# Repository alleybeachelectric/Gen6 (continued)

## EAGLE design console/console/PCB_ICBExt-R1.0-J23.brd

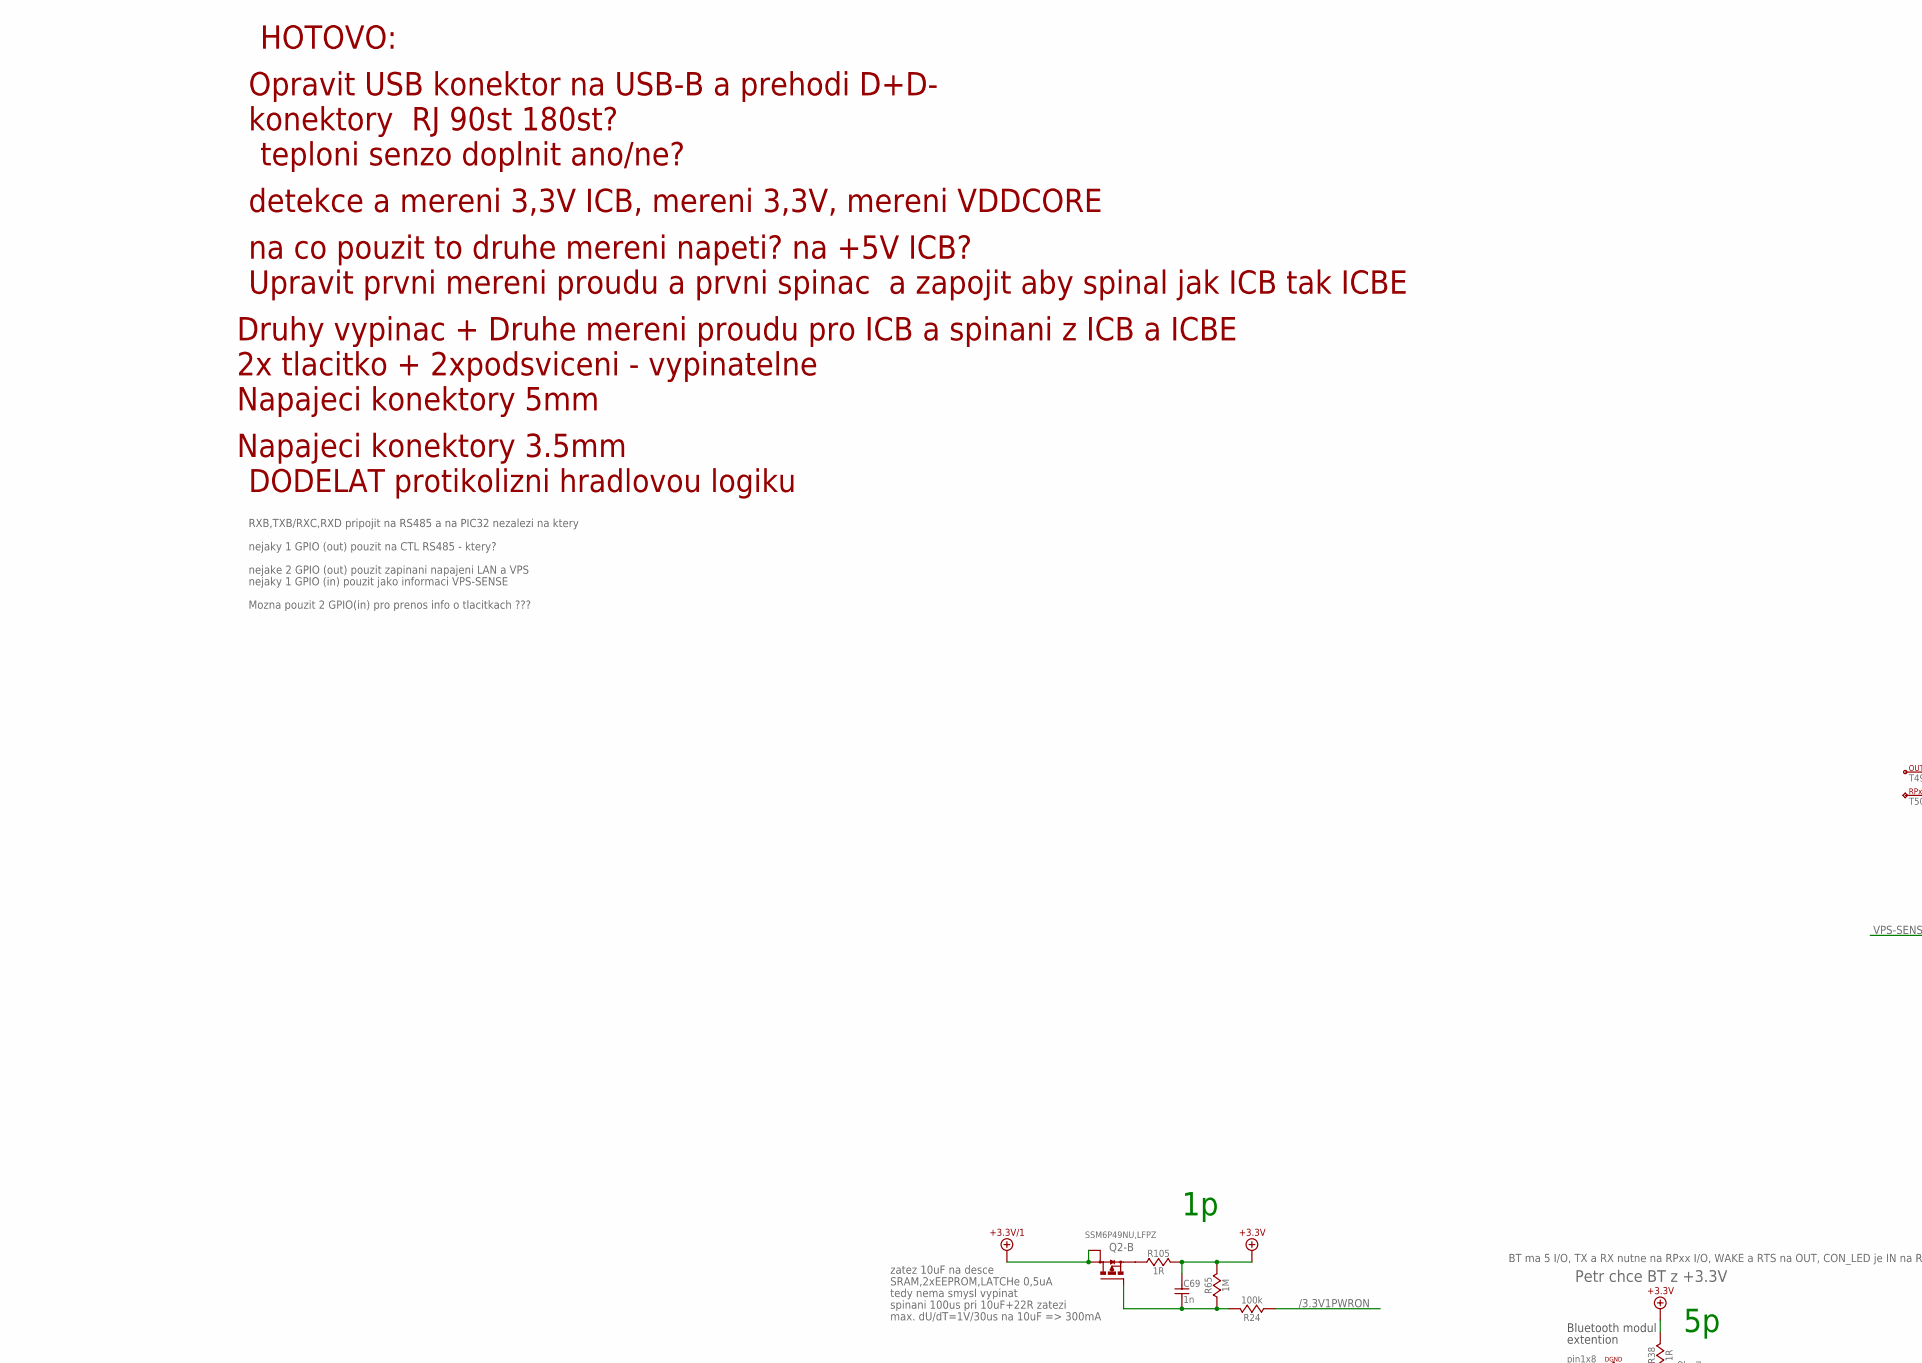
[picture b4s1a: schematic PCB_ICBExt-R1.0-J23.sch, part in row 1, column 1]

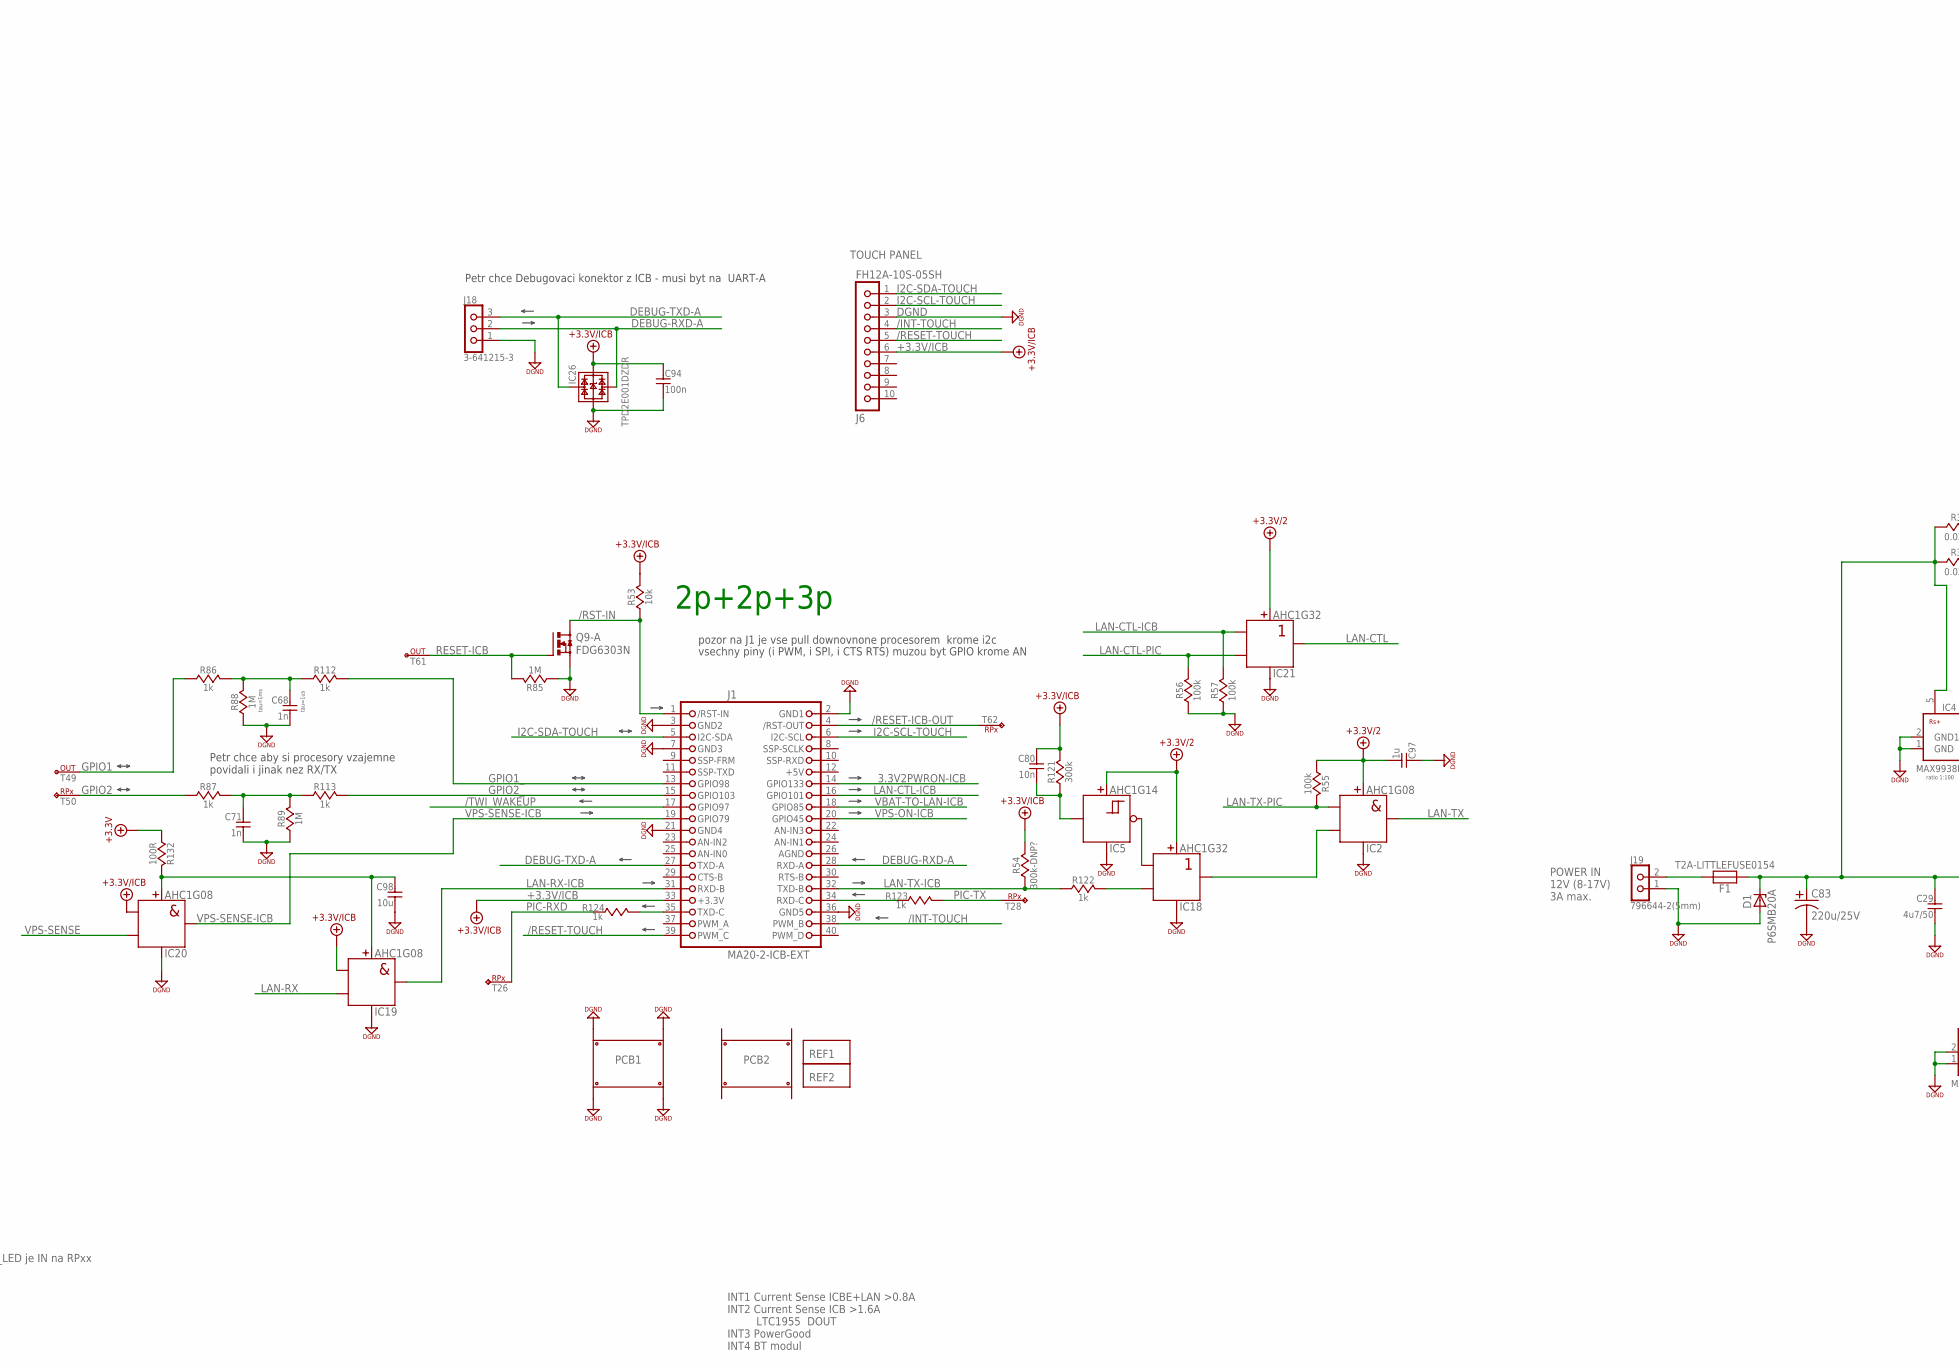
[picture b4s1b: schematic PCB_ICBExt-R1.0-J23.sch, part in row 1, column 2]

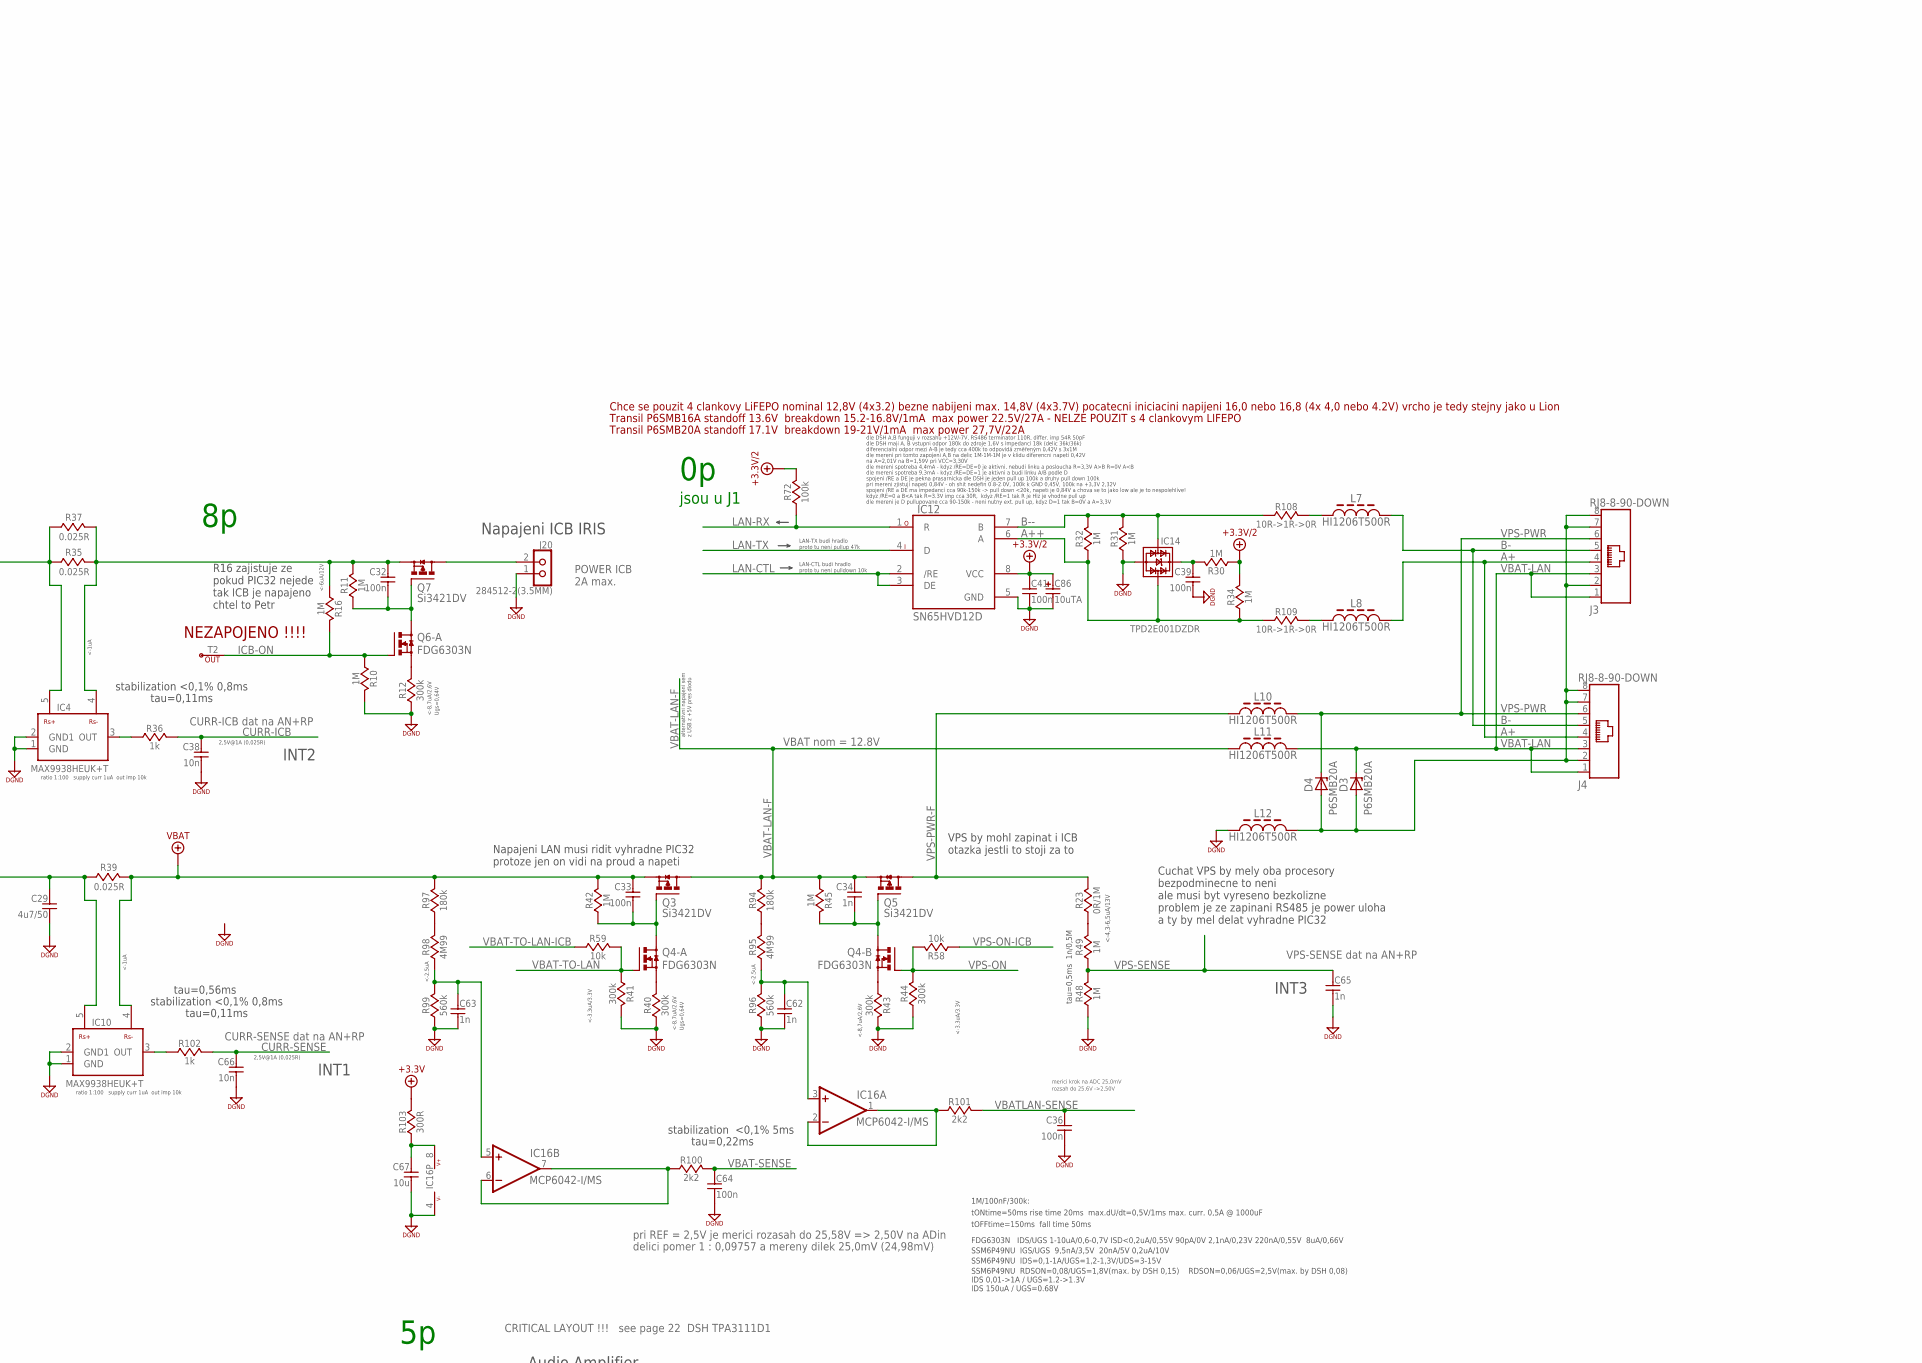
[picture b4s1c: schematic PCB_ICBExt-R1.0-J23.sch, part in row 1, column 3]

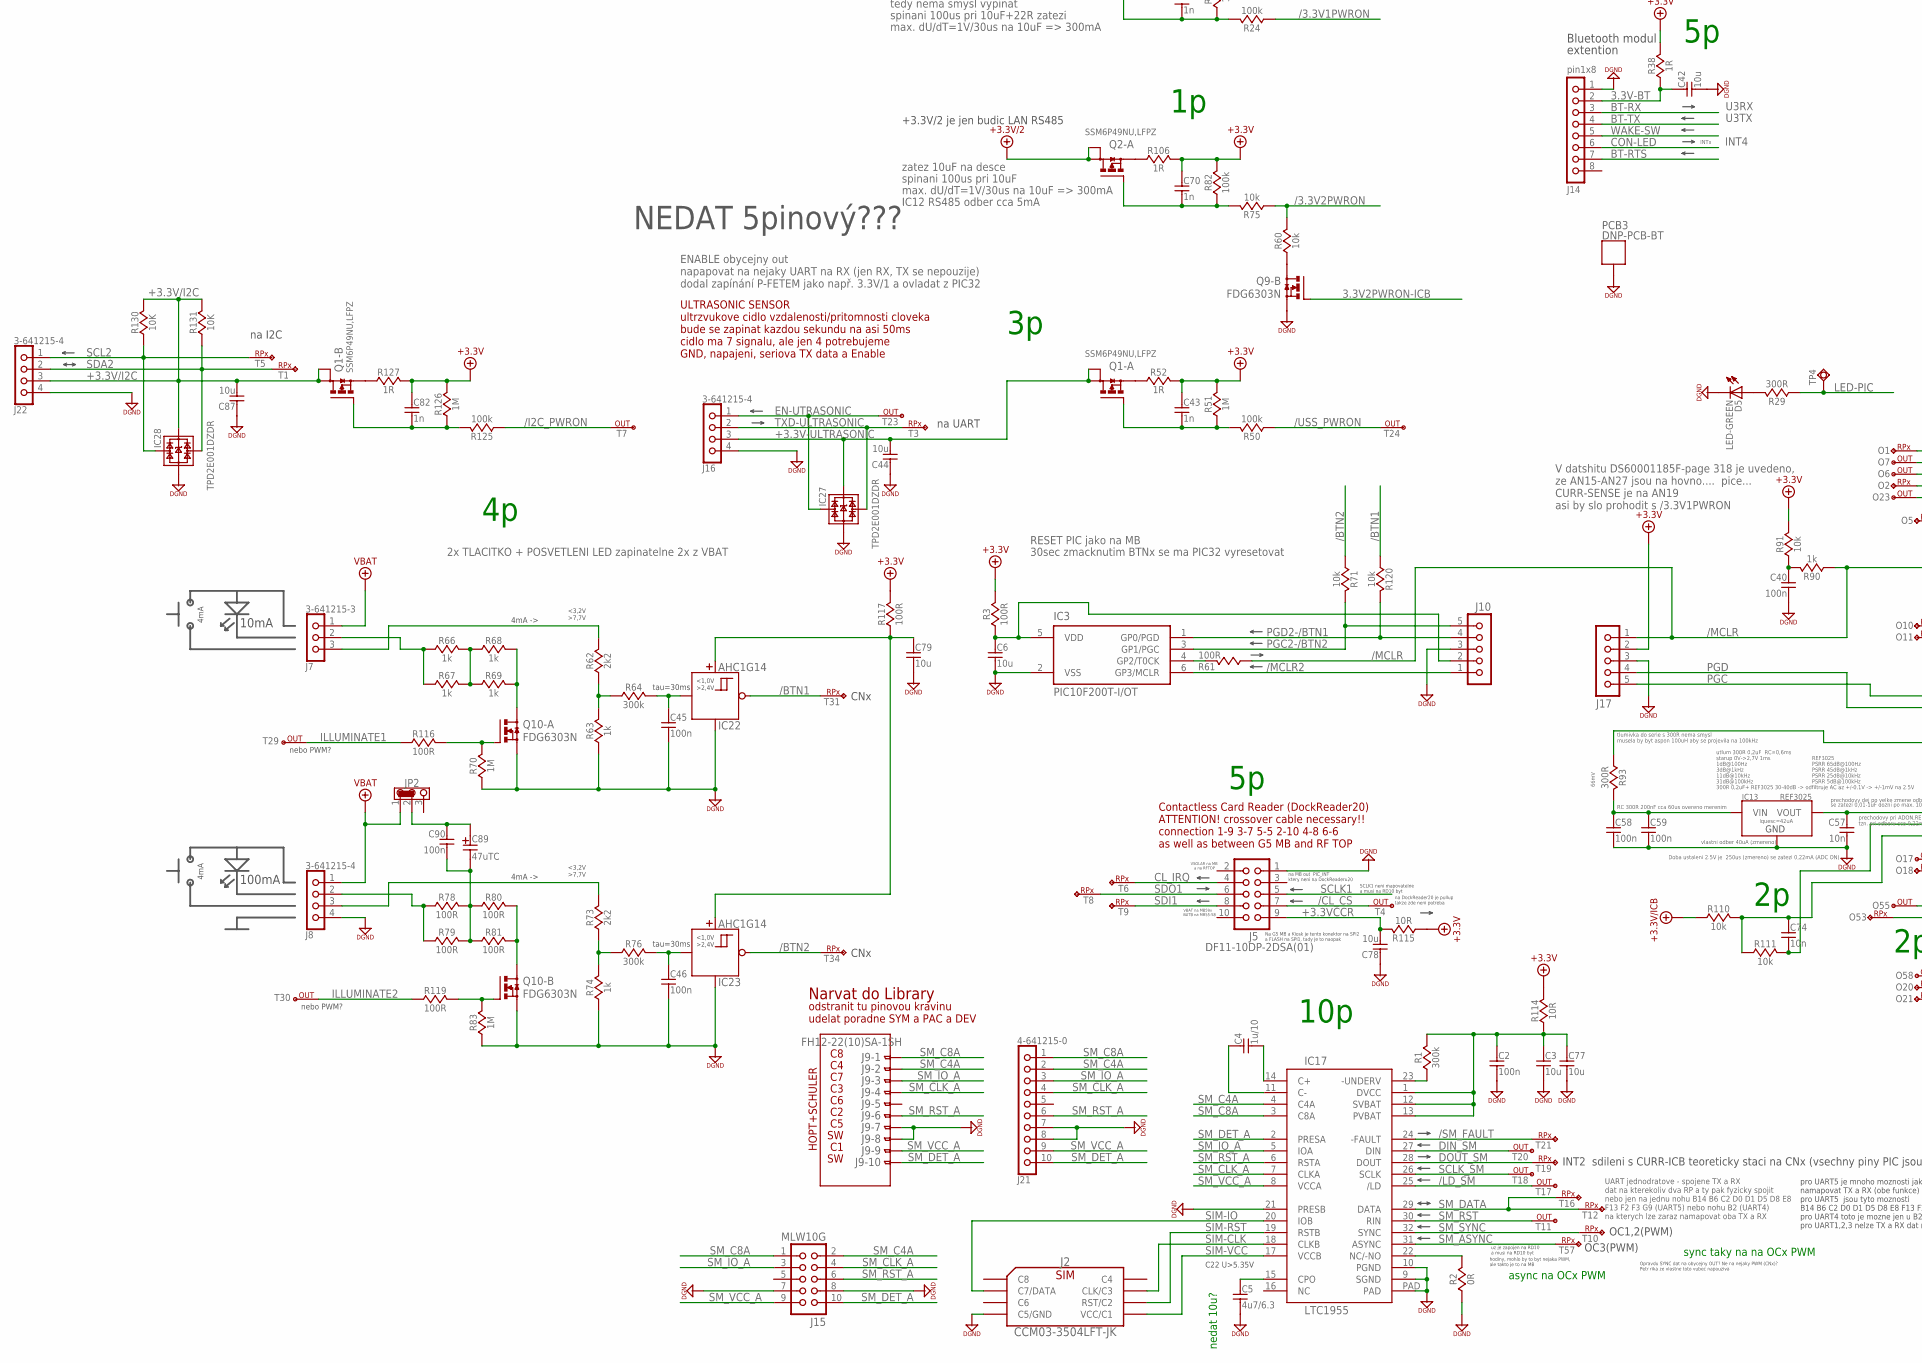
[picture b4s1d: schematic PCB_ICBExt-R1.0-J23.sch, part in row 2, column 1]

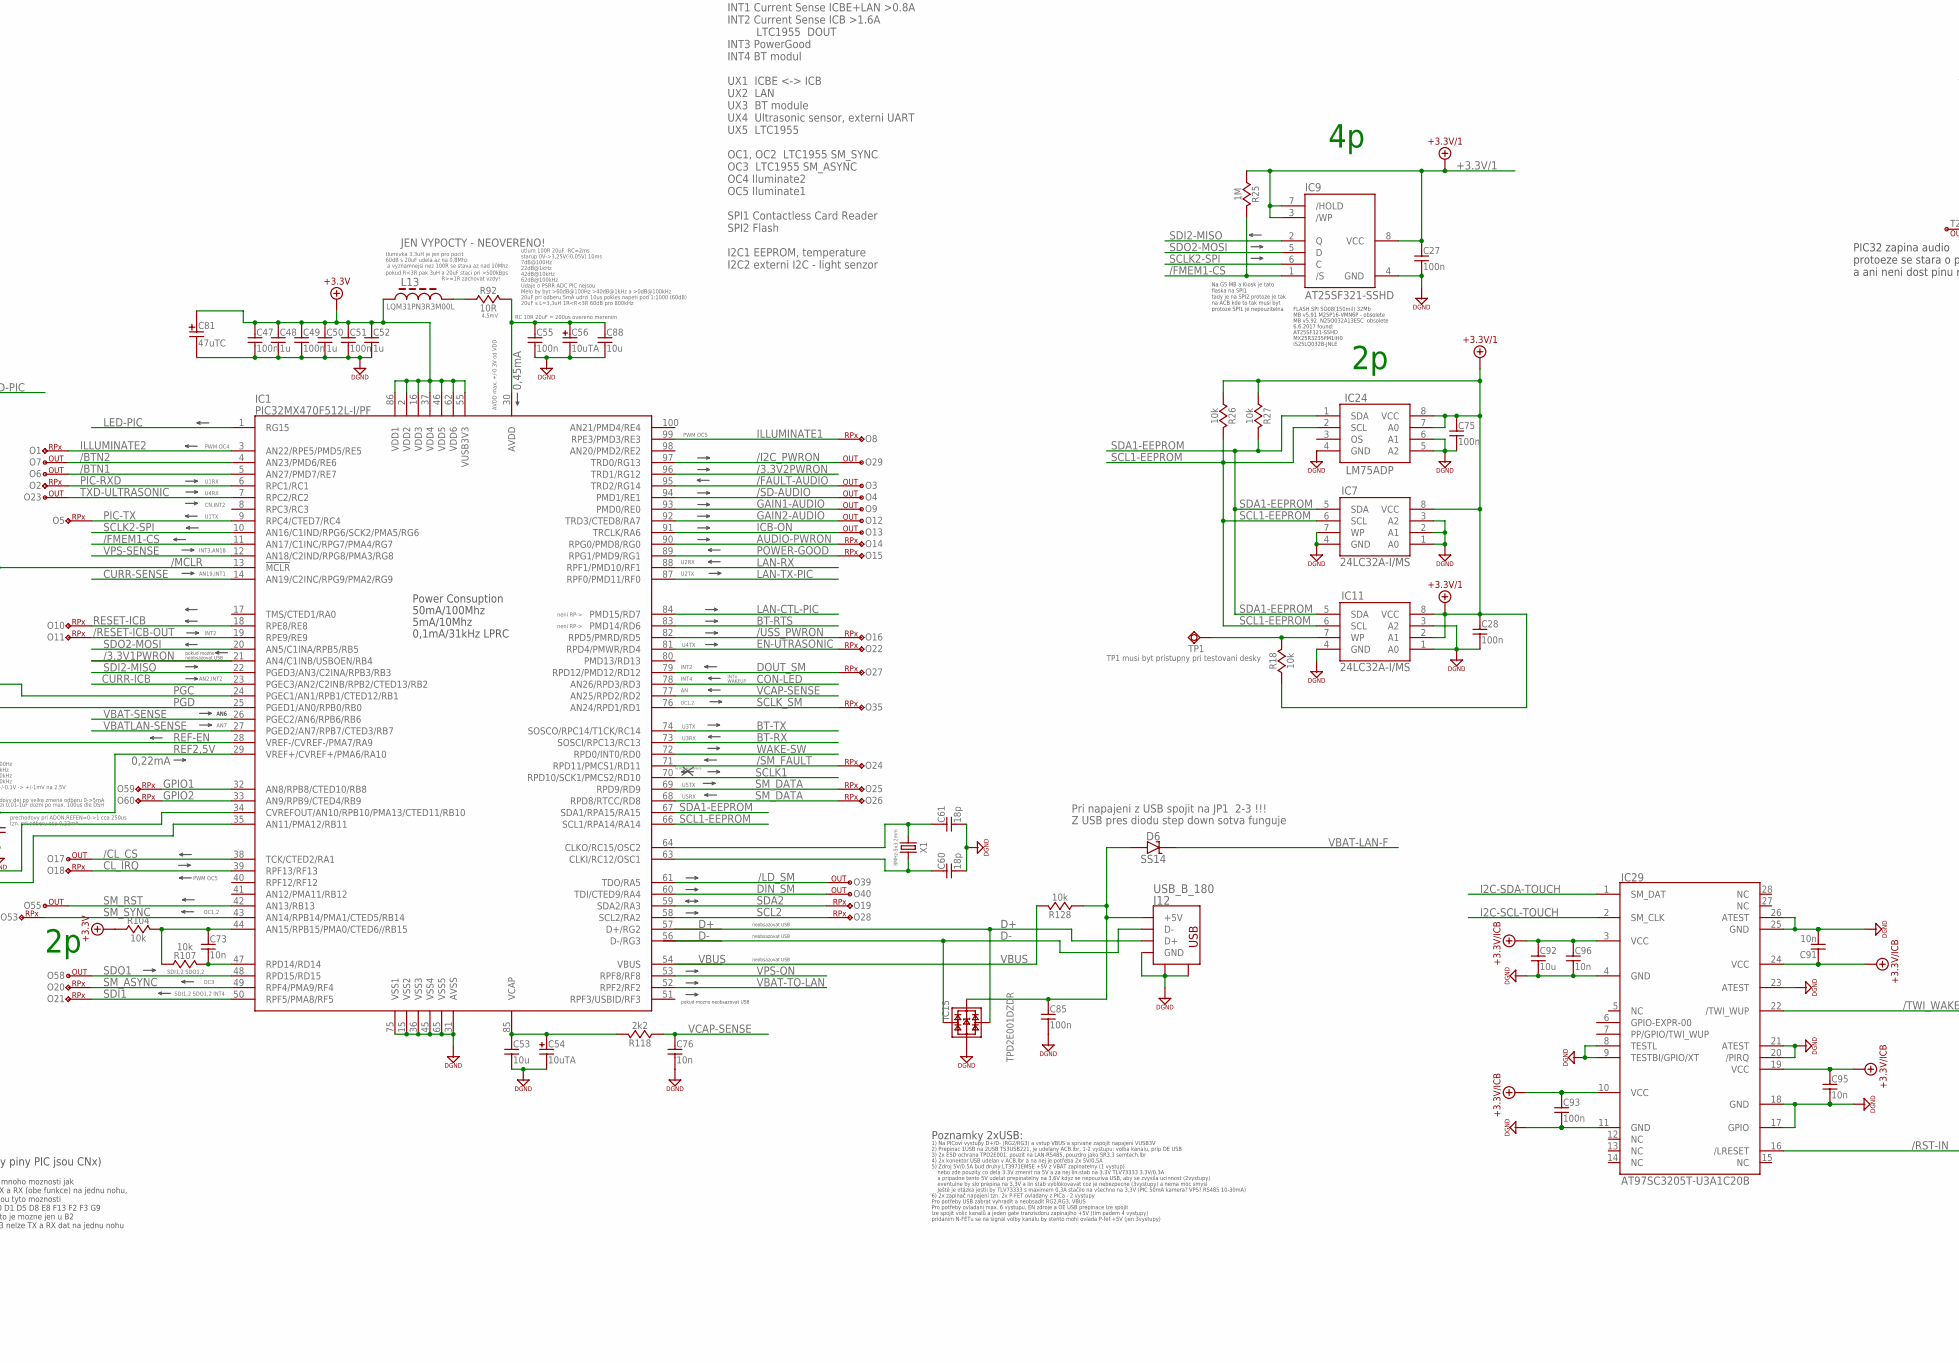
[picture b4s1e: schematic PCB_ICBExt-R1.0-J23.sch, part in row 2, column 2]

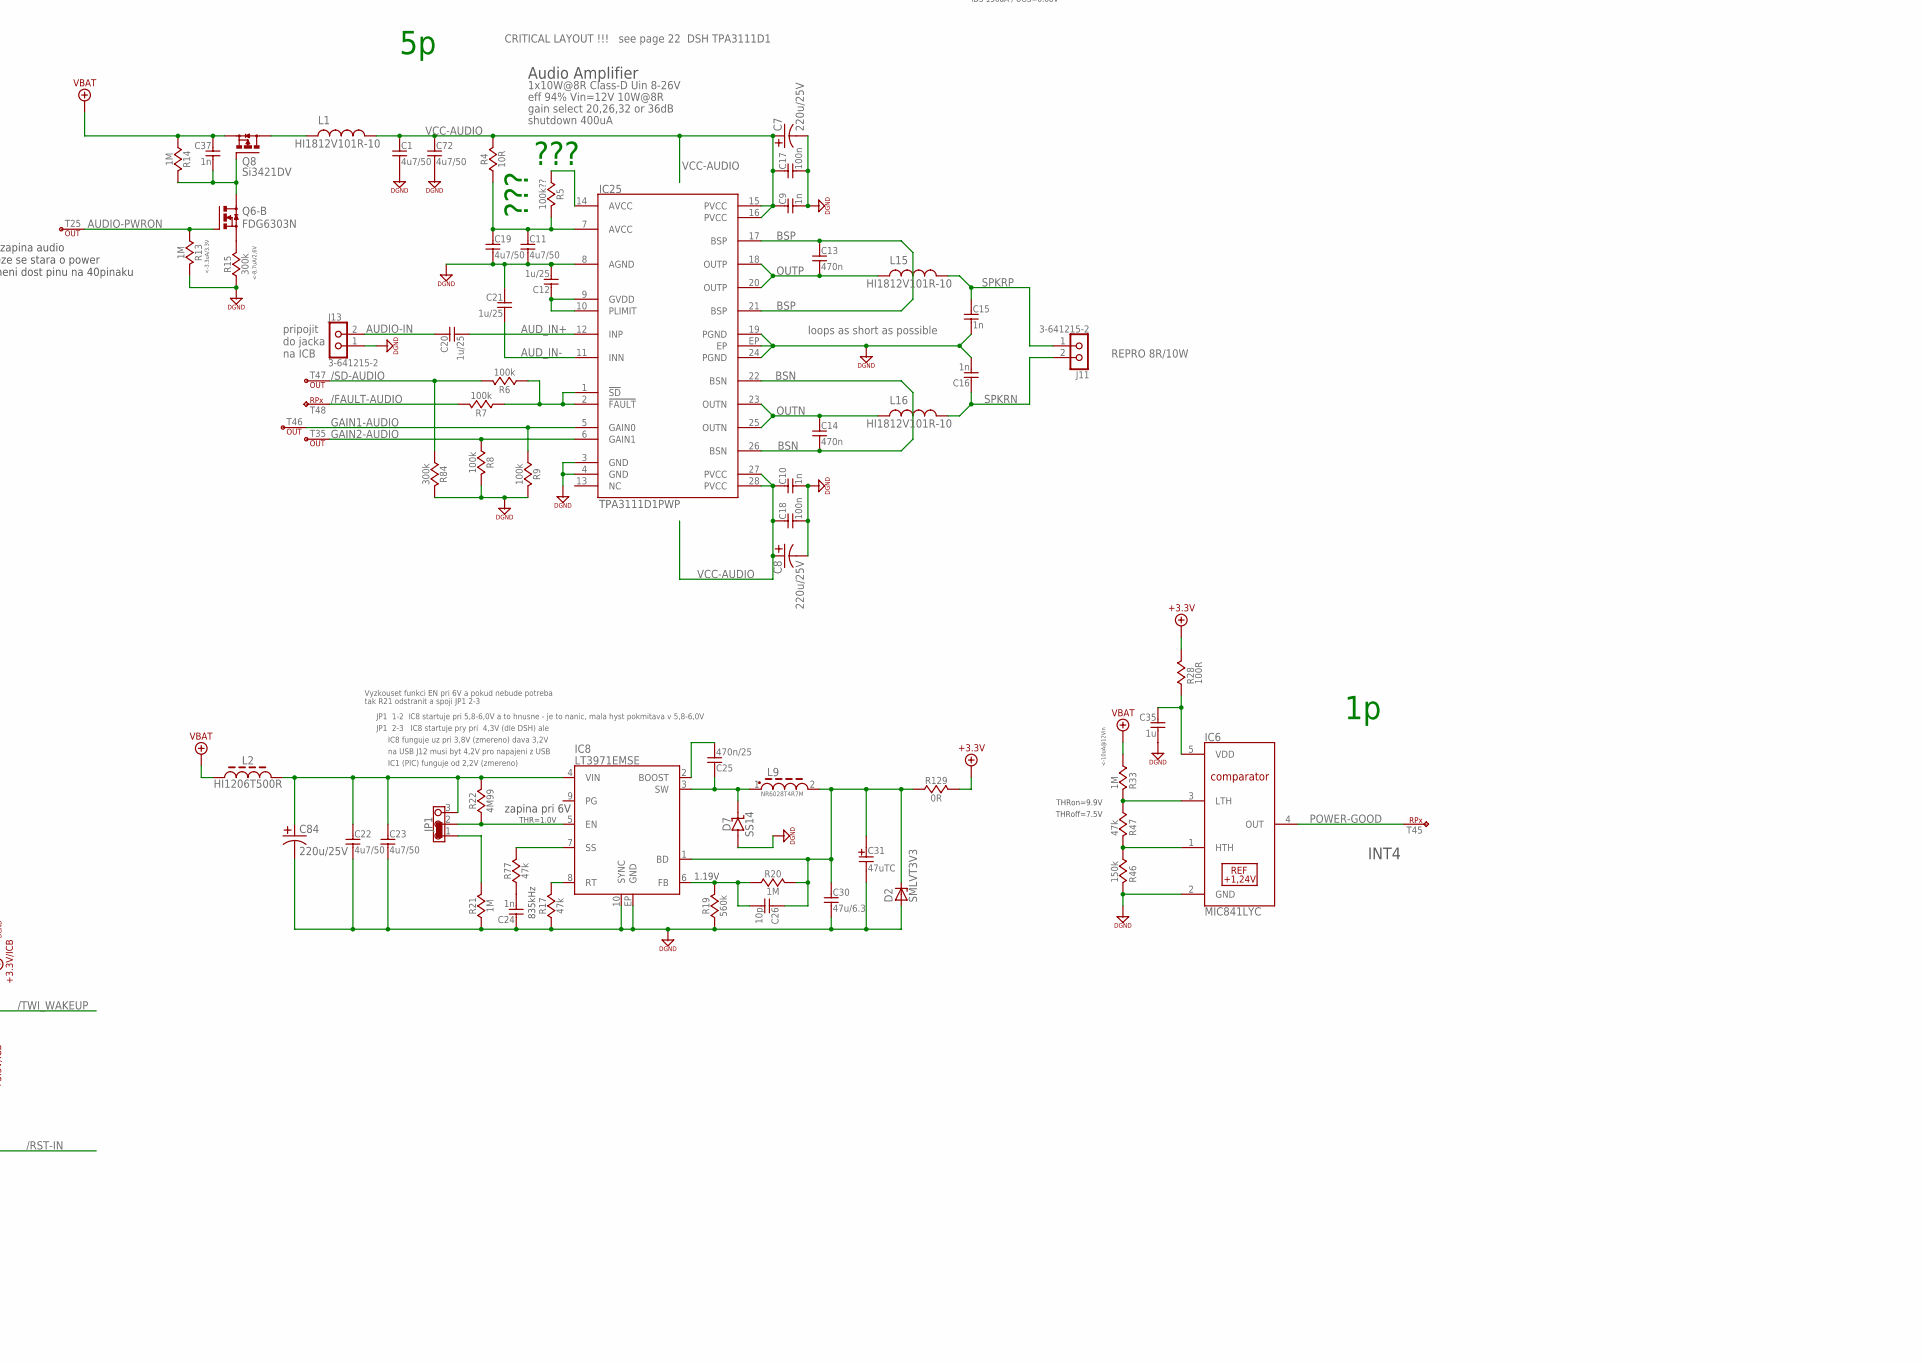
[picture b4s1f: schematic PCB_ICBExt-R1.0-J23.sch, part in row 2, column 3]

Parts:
C1, C11, C19, C22, C23, C29, C72: 4u7/50; 1206
C2, C17, C18, C27, C28, C32, C33, C36, C39, C40, C41, C45, C46, C47, C49, C51, C55, C58, C59, C64, C75, C85, C90, C93, C94: 100n; 0603
C3, C6, C42, C44, C53, C67, C77, C78, C79, C87, C88, C92, C98: 10u; 0603
C4: 1u/10; 0603
C5: 4u7/6.3; 0603
C7, C8, C83, C84: 220u/25V; CAP_8MM_DIA_SMT
C9, C10, C15, C16, C24, C34, C37, C43, C62, C63, C65, C68, C69, C70, C71, C82: 1n; 0603
C12, C20, C21: 1u/25; 0603
C13, C14: 470n; 0603
C25: 470n/25; 0603
C26: 10p; 0603
C30: 47u/6.3; 1206
C31, C81, C89: 47uTC; CT-C
C35, C48, C50, C52, C97: 1u; 0603
C38, C57, C66, C73, C74, C76, C80, C91, C95, C96: 10n; 0603
C54, C56, C86: 10uTA; 1206-POL-C
C60, C61: 18p; 0603
D1, D3, D4: P6SMB20A; SMB
D2: SMLVT3V3; SMA
D5: LED-GREEN; 0805-POL-D
D6, D7: SS14; SMA
F1: T2A-LITTLEFUSE0154; LITTLEFUSE0154
IC1: PIC32MX470F512L-I/PF; TQFP100_14X14_0,5MM
IC2, IC19, IC20: AHC1G08; SC70-5,SOT353,TSSOP5
IC3: PIC10F200T-I/OT; SOT23-6
IC4, IC10: MAX9938HEUK+T; SOT23-5
IC5, IC22, IC23: AHC1G14; SC70-5,SOT353,TSSOP5
IC6: MIC841LYC; SC-70-5
IC7, IC11: 24LC32A-I/MS; MSOP-08
IC8: LT3971EMSE; MSOP10EXP
IC9: AT25SF321-SSHD; SO-08
IC12: SN65HVD12D; SO08
IC13: REF3025; SOT23
IC14, IC15, IC26, IC27, IC28: TPD2E001DZDR; SOT-143
IC16: MCP6042-I/MS; MSOP-08
IC17: LTC1955; QFN32
IC18, IC21: AHC1G32; SC70-5,SOT353,TSSOP5
IC24: LM75ADP; TSSOP08-3
IC25: TPA3111D1PWP; TSSOP28_EP
IC29: AT97SC3205T-U3A1C20B; TSSOP28
J1: MA20-2-ICB-EXT; MA20-2
J2: CCM03-3504LFT-JK
J3, J4: RJ8-8-90-DOWN
J5: DF11-10DP-2DSA(01); DF11-10DP-2DSA
J6: FH12A-10S-05SH
J7, J18: 3-641215-3
J8, J16, J22: 3-641215-4
J9: FH12-22(10)SA-1SH; CON-FPC-1.0MM-10POS
J10, J17: DNP-open-hole; MA05-1
J11, J13: 3-641215-2
J12: USB_B_180; USB_B_90
J14: pin1x8; MA08-1-MALE
J15: MLW10G; MLW10G-5X2
J19: 796644-2(5mm); 796644-2-5MM
J20: 284512-2(3.5MM); 284512-2-3,5MM
J21: 4-641215-0
JP1, JP2: JP3CLOSE12
L1, L15, L16: HI1812V101R-10; L1812; MFR_PN HI1812V101R-10
L2, L7, L8, L10, L11, L12: HI1206T500R; 1206
L9: NR6028T4R7M; NR6028
L13: LQM31PN3R3M00L; 1206
O1, O2, O5, O8, O10, O11, O14, O15, O16, O18, O19, O20, O21, O22, O24, O25, O26, O27, O28, O35, O53, O59, O60: PIC-RPX; TEMP-PAD
O3, O4, O6, O7, O9, O12, O13, O17, O23, O29, O39, O40, O55, O58: PIC-OUT; TEMP-PAD
PCB1: PCB-ICBE
PCB2: NDP-PCB-ICB; PCB-ICB
PCB3: DNP-PCB-BT; BT_MODULE_BRD
Q1, Q2: SSM6P49NU,LFPZ; MICRO_FET
Q3, Q5, Q7, Q8: Si3421DV; SSOT-6
Q4, Q6, Q9, Q10: FDG6303N; SC70-6
R1, R12, R15, R40, R41, R43, R44, R64, R76, R84, R121: 300k; 0603
R2, R129: 0R; 0603
R3, R28, R61, R78, R79, R80, R81, R116, R117, R119, R132: 100R; 0603
R4, R92, R114, R115: 10R; 0603
R5: 100k??; 0603
R6, R7, R8, R9, R24, R50, R55, R56, R57, R72, R82, R125: 100k; 0603
R10, R11, R13, R14, R16, R20, R21, R25, R30, R31, R32, R33, R34, R42, R45, R48, R49, R51, R65, R70, R83, R85, R88, R89, R126: 1M; 0603
R17, R47, R77: 47k; 0603
R18, R26, R27, R53, R58, R59, R60, R71, R75, R91, R104, R107, R110, R111, R120, R128: 10k; 0603
R19, R96, R99: 560k; 0603
R22, R95, R98: 4M99; 0603
R23: 0R/1M; 0603
R29, R93, R103: 300R; 0603
R35, R37, R39: 0.025R; 0805
R36, R63, R66, R67, R68, R69, R74, R86, R87, R90, R102, R112, R113, R122, R123, R124: 1k; 0603
R38, R52, R105, R106, R127: 1R; 0805
R46: 150k; 0603
R54: 300k-DNP?; 0603
R62, R73, R100, R101, R118: 2k2; 0603
R94, R97: 180k; 0603
R108, R109: 10R->1R->0R; 0603
R130, R131: 10K; 0603
REF1, REF2: REF
T1, T3, T5, T6, T8, T9, T10, T12, T16, T19, T21, T26, T28, T31, T34, T45, T48, T50, T57, T62: PIC-RPX; TEMP-PAD
T2, T4, T7, T11, T17, T18, T20, T23, T24, T25, T29, T30, T35, T46, T47, T49, T61: PIC-OUT; TEMP-PAD
TP1: DNP-TestPoint; SMD_ROUND_1MM
TP4: DNP-TestPoint; TH_ROUND_14MM08MM
X1: 8MHz-5x3.2mm; 7B

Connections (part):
3.3V2PWRON-ICB: J1.14 (GPIO133), Q9.5 (G)
3.3V-BT: C42.1, J14.2, R38.1
+3,3V-FILT: C35.1, IC6.5 (VDD), R28.1
+3.3V: C43.1, C47.1, C48.1, C49.1, C50.1, C51.1, C52.1, C69.1, C70.1, C81.+, C82.1, IC1.2 (VDD2), IC1.16 (VDD3), IC1.37 (VDD4), IC1.46 (VDD5), IC1.55 (VUSB3V3), IC1.62 (VDD6), IC1.86 (VDD1), J17.2, L13.1, R3.1, R28.2, R38.2, R51.1, R52.2, R65.1, R82.1, R91.2, R103.2, R104.1, R105.2, R106.2, R114.1, R115.2, R117.2, R126.1, R127.2, R129.1, R132.1
+3.3V-ULTRASONIC: C44.2, IC27.4, J16.3, Q1.6 (D), Q1.P1 (D1)
+3.3V/1: C27.1, C28.1, C75.1, IC7.8 (VCC), IC9.3 (/WP), IC9.7 (/HOLD), IC9.8 (VCC), IC11.2 (A1), IC11.8 (VCC), IC24.7 (A0), IC24.8 (VCC), Q2.3 (D), Q2.P2 (D1), R18.1, R25.2, R26.1, R27.1
+3.3V/2: C41.1, C86.+, C97.2, IC2.5 (VCC), IC5.5 (VCC), IC12.8 (VCC), IC18.5 (VCC), IC21.5 (VCC), Q2.6 (D), Q2.P1 (D1), R30.2, R34.1, R55.1, R72.1
+3.3V/I2C: C87.2, IC28.4, J22.3, Q1.3 (D), Q1.P2 (D1), R130.1, R131.1
+3.3V/ICB: C80.1, C91.1, C92.1, C93.1, C94.1, C95.1, C96.1, IC19.1 (A), IC20.1 (A), IC26.4, IC29.3 (VCC), IC29.10 (VCC), IC29.19 (VCC), IC29.24 (VCC), J1.33 (+3.3V), J6.6, R53.2, R54.2, R110.1, R121.2
+3.3VCCR: C78.2, J5.9, R115.1
/3.3V1PWRON: IC1.21 (AN4/C1INB/USBOEN/RB4), R24.2
/3.3V2PWRON: IC1.96 (TRD1/RG12), R60.2, R75.2
/BTN1: IC1.5 (AN27/PMD7/RE7), IC22.4 (OUT), O6.P$1, R120.2, T31.P$1
/BTN2: IC1.4 (AN23/PMD6/RE6), IC23.4 (OUT), O7.P$1, R71.2, T34.P$1
/CL_CS: IC1.38 (TCK/CTED2/RA1), J5.7, O17.P$1, T4.P$1
/FAULT-AUDIO: IC1.95 (TRD2/RG14), O3.P$1, R7.1, T48.P$1
/FMEM1-CS: IC1.11 (AN17/C1INC/RPG7/PMA4/RG7), IC9.1 (/S), R25.1
/I2C_PWRON: IC1.97 (TRD0/RG13), O29.P$1, R125.2, T7.P$1
/INT-TOUCH: J1.38 (PWM_B), J6.4
/LD_SM: IC1.61 (TDO/RA5), IC17.25 (/LD), O39.P$1, T17.P$1
/MCLR: IC1.13 (!MCLR), J17.1, R61.2, R90.2
/MCLR2: IC3.6 (GP3/MCLR), J10.1
/RESET-ICB-OUT: IC1.19 (RPE9/RE9), J1.4 (/RST-OUT), O11.P$1, T62.P$1
/RESET-TOUCH: J1.39 (PWM_C), J6.5
/RST-IN: IC29.16 (/LRESET), J1.1 (/RST-IN), Q9.6 (D), R53.1
/SD-AUDIO: IC1.94 (PMD1/RE1), O4.P$1, R6.1, R84.2, T47.P$1
/SM_FAULT: IC1.71 (RPD11/PMCS1/RD11), IC17.24 (-FAULT), O24.P$1, T21.P$1
/TWI_WAKEUP: IC29.22 (/TWI_WUP), J1.17 (GPIO97)
/USS_PWRON: IC1.82 (RPD5/PMRD/RD5), O16.P$1, R50.2, T24.P$1
A+: J3.4, J4.4, L8.2
A++: IC12.6 (A), IC14.3, R32.2, R34.2, R109.2
AUD-AVCC: C11.1, C19.1, IC25.7 (AVCC), R4.2, R5.1
AUDIO-IN: C20.1, J13.2
AUDIO-PWRON: IC1.90 (RPG0/PMD8/RG0), O14.P$1, Q6.5 (G), R13.1, T25.P$1
AUD_AMP_FAULT#: IC25.1 (!SD), IC25.2 (!FAULT), R6.2, R7.2
AUD_GVDD: C12.1, IC25.9 (GVDD), IC25.10 (PLIMIT)
AUD_IN+: C20.2, IC25.12 (INP)
AUD_IN-: C21.2, IC25.11 (INN)
AVDD: C55.1, C56.+, C88.1, IC1.30 (AVDD), R92.2
B-: J3.5, J4.5, L7.2
B--: IC12.7 (B), IC14.2, R31.1, R32.1, R108.2
BSN: C14.2, IC25.22 (BSN), IC25.26 (BSN)
BSP: C13.1, IC25.17 (BSP), IC25.21 (BSP)
BT-RTS: IC1.83 (PMD14/RD6), J14.7
BT-RX: IC1.73 (SOSCI/RPC13/RC13), J14.3
BT-TX: IC1.74 (SOSCO/RPC14/T1CK/RC14), J14.4
CL_IRQ: IC1.39 (RPF13/RF13), J5.4, O18.P$1, T6.P$1
CON-LED: IC1.78 (AN26/RPD3/RD3), J14.6
CURR-ICB: C38.1, IC1.23 (PGEC3/AN2/C2INB/RPB2/CTED13/RB2), R36.2
CURR-SENSE: C66.1, IC1.14 (AN19/C2INC/RPG9/PMA2/RG9), R102.2
D+: IC1.57 (D+/RG2), IC15.3, J12.3_D+ (D+)
D-: IC1.56 (D-/RG3), IC15.2, J12.2_D- (D-)
DEBUG-RXD-A: IC26.3, J1.28 (RXD-A), J18.2
DEBUG-TXD-A: IC26.2, J1.27 (TXD-A), J18.3
DGND: C1.2, C2.2, C3.2, C5.2, C6.2, C7.2, C8.2, C9.2, C10.2, C11.2, C12.2, C15.2, C16.2, C17.2, C18.2, C19.2, C21.1, C22.2, C23.2, C24.1, C27.2, C28.2, C29.2, C30.2, C31.-, C35.2, C36.2, C38.2, C39.2, C40.2, C41.2, C42.2, C44.1, C45.2, C46.2, C47.2, C48.2, C49.2, C50.2, C51.2, C52.2, C53.2, C54.-, C55.2, C56.-, C57.2, C58.2, C59.2, C60.2, C61.2, C62.2, C63.2, C64.2, C65.2, C66.2, C67.2, C68.2, C71.2, C72.2, C75.2, C76.2, C77.2, C78.1, C79.2, C81.-, C83.2, C84.2, C85.2, C86.-, C87.1, C88.2, C91.2, C92.2, C93.2, C94.2, C95.2, C96.2, C97.1, C98.2, D1.A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
DGND-F: D3.A, D4.A, J3.2, J3.7, J3.8, J4.2, J4.7, J4.8, L12.2
DIN_SM: IC1.60 (TDI/CTED9/RA4), IC17.27 (DIN), O40.P$1, T20.P$1
DOUT_SM: IC1.79 (RPD12/PMD12/RD12), IC17.28 (DOUT), O27.P$1, T19.P$1
EN-UTRASONIC: IC1.81 (RPD4/PMWR/RD4), IC27.2, J16.1, O22.P$1, T23.P$1
GAIN1-AUDIO: IC1.93 (PMD0/RE0), IC25.5 (GAIN0), O9.P$1, R9.2, T46.P$1
GAIN2-AUDIO: IC1.92 (TRD3/CTED8/RA7), IC25.6 (GAIN1), O12.P$1, R8.2, T35.P$1
GATE-Q3: C33.2, Q3.3 (G), Q4.6 (D), R42.2
GATE-Q5: C34.2, Q4.3 (D), Q5.3 (G), R45.2
GATE-Q7: C32.2, Q6.6 (D), Q7.3 (G), R11.2
GATE-Q8: C37.2, Q6.3 (D), Q8.3 (G), R14.2
GPIO1: IC1.32 (AN8/RPB8/CTED10/RB8), O59.P$1, R86.1, T49.P$1
GPIO1_: J1.13 (GPIO98), R112.2
GPIO2: IC1.33 (AN9/RPB9/CTED4/RB9), O60.P$1, R87.1, T50.P$1
GPIO2_: J1.15 (GPIO103), R113.2
I2C-SCL-TOUCH: IC29.2 (SM_CLK), J1.6 (I2C-SCL), J6.2
I2C-SDA-TOUCH: IC29.1 (SM_DAT), J1.5 (I2C-SDA), J6.1
ICB-ON: IC1.91 (TRCLK/RA6), O13.P$1, Q6.2 (G), R10.1, R16.2, T2.P$1
ILLUMINATE1: IC1.99 (RPE3/PMD3/RE3), O8.P$1, R116.1, T29.P$1
ILLUMINATE2: IC1.3 (AN22/RPE5/PMD5/RE5), O1.P$1, R119.1, T30.P$1
LAN-CTL: IC12.2 (/RE), IC12.3 (DE), IC21.4 (Y)
LAN-CTL-ICB: IC21.1 (A), J1.16 (GPIO101), R57.2
LAN-CTL-PIC: IC1.84 (PMD15/RD7), IC21.2 (B), R56.2
LAN-RX: IC1.88 (RPF1/PMD10/RF1), IC12.1 (R), IC19.2 (B), R72.2
LAN-RX-ICB: IC19.4 (Y), J1.31 (RXD-B)
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
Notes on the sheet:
MB v5.91 M25P16-VMN6P - obsolete
MB v5.92 N25Q032A13ESC obsolete
THRon=9.9V
THRoff=7.5V
<-8,7uA/2,6V
Ugs=0,64V
<-4,3-6,5uA/13V
<-3.3uA/3.3V
tau=0,5ms 1n/0,5M
Chce se pouzit 4 clankovy LiFEPO nominal 12,8V (4x3.2) bezne nabijeni max. 14,8V (4x3.7V) pocatecni iniciacini napijeni 16,0 nebo 16,8 (4x 4,0 nebo 4.2V) vrcho je tedy stejny jako u Lion
Transil P6SMB16A standoff 13.6V breakdown 15.2-16.8V/1mA max power 22.5V/27A - NELZE POUZIT s 4 clankovym LIFEPO
Transil P6SMB20A standoff 17.1V breakdown 19-21V/1mA max power 27,7V/22A
FDG6303N IDS/UGS 1-10uA/0,6-0,7V ISD<0,2uA/0,55V 90pA/0V 2,1nA/0,23V 220nA/0,55V 8uA/0,66V
SSM6P49NU IGS/UGS 9,5nA/3,5V 20nA/5V 0,2uA/10V
SSM6P49NU IDS=0,1-1A/UGS=1,2-1,3V/UDS=3-15V
SSM6P49NU RDSON=0,08/UGS=1,8V(max. by DSH 0,15) RDSON=0,06/UGS=2,5V(max. by DSH 0,08)
tONtime=50ms rise time 20ms max.dU/dt=0,5V/1ms max. curr. 0,5A @ 1000uF
tOFFtime=150ms fall time 50ms
1M/100nF/300k:
IDS 150uA / UGS=0.68V
IDS 0,01->1A / UGS=1.2->1.3V
ratio 1:100 supply curr 1uA out imp 10k
2,5V@1A (0,025R)
AT25SF321-SSHD
MX25R3235FM1IH0
IS25LQ032B-JNLE
FLASH SPI SO08(150mil) 32Mb
6.6.2017 found:
VBAT nom = 12.8V
835kHz
1.19V
THR=1.0V
Poznamky 2xUSB:
nebo zde pouzity co dela 3.3V zmenit na 5V a za nej lin.stab na 3.3V TLV73333 3.3V/0.3A
5) Zdroj 5V/0.5A bud druhy LT3971EMSE +5V z VBAT zapinatelny (1 vystup)
a pripadne tento 5V udelat prepinatelny na 3,6V kdyz se nepouziva USB, aby se zvysila ucinnost (2vystupy)
2) Prepinac 1USB na 2USB TS3USB221, je udelany ACB.lbr, 1-2 vystupu: volba kanalu, prip OE USB
3) 2x ESD ochrana TPD2E001, pouzit na LAN-RS485, pouzdro jako SR3.3 semtech.lbr
6) 2x zapinač napajení tzn. 2x P-FET ovladany z PICa - 2 vystupy
1) Na PICovi vystupy D+/D- (RG2/RG3) a vstup VBUS a sprvane zapojit napajeni VUSB3V

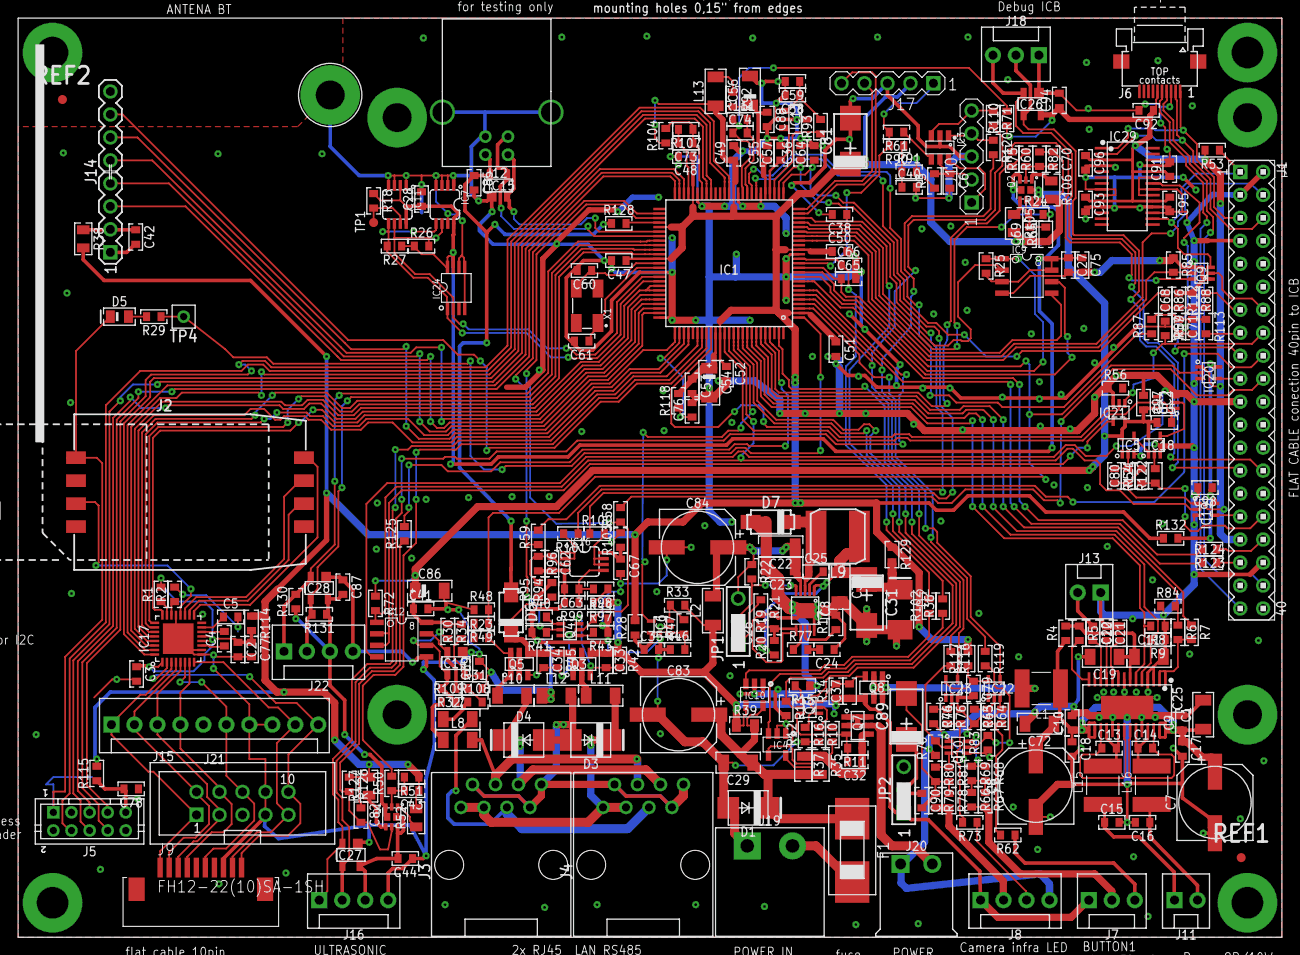
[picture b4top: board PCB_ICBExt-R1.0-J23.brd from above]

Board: 2 copper layers, 139.7 x 101.6 mm, 394 parts (0 on the bottom side), 231 nets.
